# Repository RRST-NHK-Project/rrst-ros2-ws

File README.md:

# **rrst-ros2-workspace**

**日本語** | [English](README.en.md)

## 1. 概要
NHK プロジェクトのメインリポジトリです。現在使用している ROS 2 パッケージを管理しています。大会ごとにこのリポジトリをforkして使用することを想定しています。

|  | 説明 | ビルド状況 |
|---|---|---|
| **main** | 安定版ブランチ（動作確認済み） |  |
| **develop** | 最新の開発ブランチ（開発中） |  |
| **Docker** | Docker ビルド（develop） |  |

---

## 2. 動作環境

| 項目 | 内容 |
|:---|:---|
| OS | Ubuntu 24.04 LTS |
| ROS | ROS 2 Jazzy |
| メモリ | 16 GB 以上推奨 |

> **注意**: ビルド中にフリーズする場合は、メモリ不足の可能性があります。  
> スワップ領域を追加するか、ビルドのスレッド数を制限してください。

---

## 3. はじめに

### 3.1 ワークスペースの作成
作成済みの場合はスキップしてください。

    mkdir -p ~/ros2_ws/src

### 3.2 SSH 鍵の登録
リポジトリ・サブモジュールとも **SSH** で運用しています。登録済みの場合はスキップしてください。

    ssh-keygen -t ed25519 -C "your_email@example.com"
    cat ~/.ssh/id_ed25519.pub

表示された公開鍵を GitHub の [Settings → SSH and GPG keys](https://github.com/settings/keys) で **New SSH key** から登録し、接続を確認します。

    ssh -T git@github.com

`Hi <ユーザー名>! You've successfully authenticated...` と表示されれば完了です。詳しくは [Wiki](https://github.com/RRST-NHK-Project/rrst-ros2-ws/wiki/SSH鍵の登録) を参照してください。

### 3.3 リポジトリのクローン

**main（安定版）**

    cd ~/ros2_ws/src
    git clone git@github.com:RRST-NHK-Project/rrst-ros2-ws.git .
    git submodule update --init --recursive

**develop（最新・開発中）**

    cd ~/ros2_ws/src
    git clone git@github.com:RRST-NHK-Project/rrst-ros2-ws.git -b develop .
    git submodule update --init --recursive

### 3.4 ビルド

    cd ~/ros2_ws
    colcon build

ビルドのスレッド数を指定する場合:

    cd ~/ros2_ws
    colcon build --parallel-workers 4

---

## 4. クレジット
Developed by NHK Project, RRST, Ritsumeikan University, Japan (2024)
- 公式サイト: https://www.rrst.jp
- X (Twitter): https://x.com/RRST_BKC

---

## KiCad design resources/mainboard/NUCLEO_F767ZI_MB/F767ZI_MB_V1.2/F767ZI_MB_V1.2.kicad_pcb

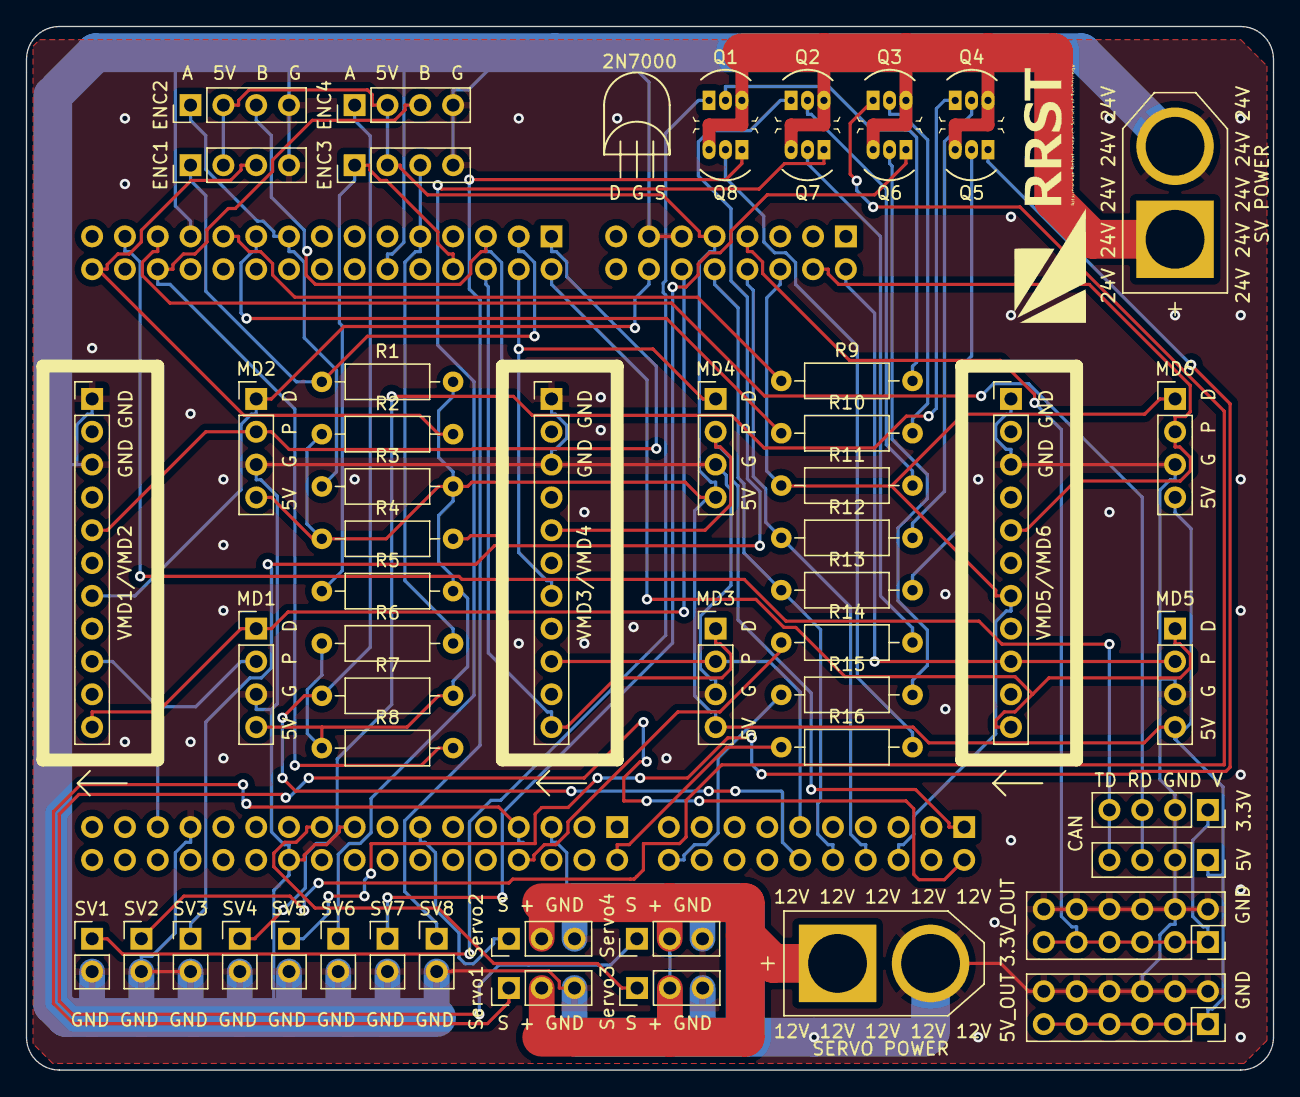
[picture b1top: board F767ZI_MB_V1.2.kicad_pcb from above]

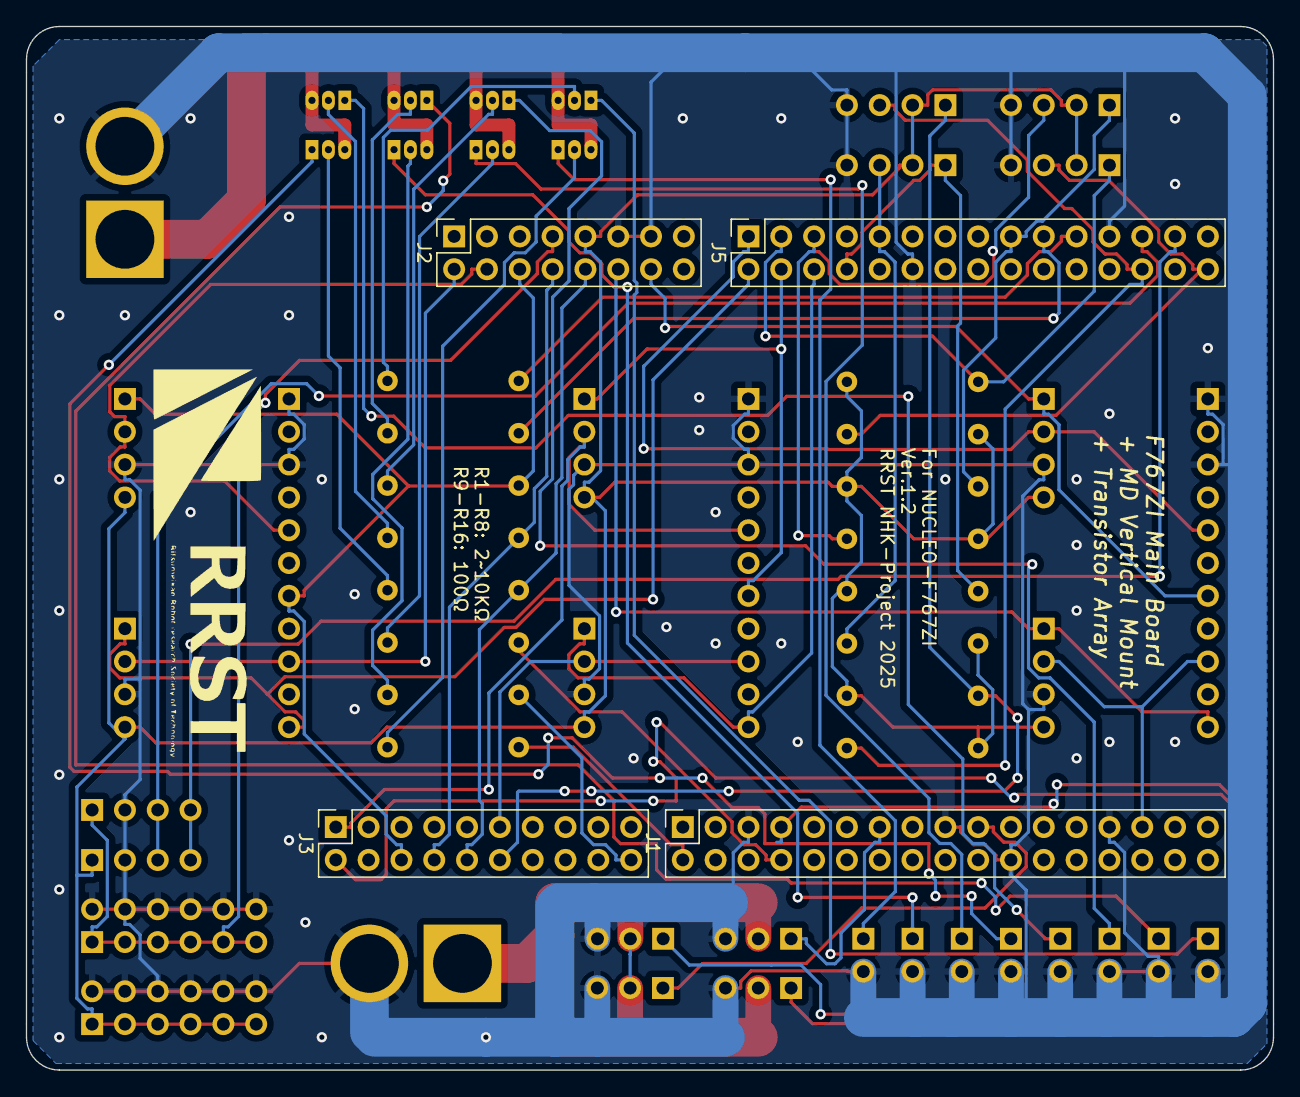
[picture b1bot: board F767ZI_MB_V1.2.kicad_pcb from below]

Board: 2 copper layers, 96.5 x 80.8 mm, 59 parts (4 on the bottom side), 54 nets.

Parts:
3.3V: CAN3.3V; PinSocket_1x04_P2.54mm_Vertical
3.3V_OUT: 3.3V_OUT; PinSocket_2x06_P2.54mm_Vertical
5V: CAN5V; PinSocket_1x04_P2.54mm_Vertical
5V_OUT: 5V_OUT; PinSocket_2x06_P2.54mm_Vertical
ENC1: ENC1; PinHeader_1x04_P2.54mm_Vertical
ENC2: ENC2; PinHeader_1x04_P2.54mm_Vertical
ENC3: ENC3; PinHeader_1x04_P2.54mm_Vertical
ENC4: ENC4; PinHeader_1x04_P2.54mm_Vertical
J1: Conn_02x17_Odd_Even; PinHeader_2x17_P2.54mm_Vertical
J2: Conn_02x08_Odd_Even; PinHeader_2x08_P2.54mm_Vertical
J3: Conn_02x10_Odd_Even; PinHeader_2x10_P2.54mm_Vertical
J5: Conn_02x15_Odd_Even; PinHeader_2x15_P2.54mm_Vertical
MD1: MD1; PinHeader_1x04_P2.54mm_Vertical
MD2: MD2; PinHeader_1x04_P2.54mm_Vertical
MD3: MD3; PinHeader_1x04_P2.54mm_Vertical
MD4: MD4; PinHeader_1x04_P2.54mm_Vertical
MD5: MD5; PinHeader_1x04_P2.54mm_Vertical
MD6: MD6; PinHeader_1x04_P2.54mm_Vertical
Q1, Q2, Q3, Q4, Q5, Q6, Q7, Q8: 2N7000; TO-92-3
R1, R2, R3, R4, R5, R6, R7, R8, R9, R10, R11, R12, R13, R14, R15, R16: R; R_Axial_DIN0207_L6.3mm_D2.5mm_P10.16mm_Horizontal
SERVO POWER: XT60-M; AMASS_XT60-M
SV1: SV1; PinHeader_1x02_P2.54mm_Vertical
SV2: SV2; PinHeader_1x02_P2.54mm_Vertical
SV3: SV3; PinHeader_1x02_P2.54mm_Vertical
SV4: SV4; PinHeader_1x02_P2.54mm_Vertical
SV5: SV5; PinHeader_1x02_P2.54mm_Vertical
SV6: SV6; PinHeader_1x02_P2.54mm_Vertical
SV7: SV7; PinHeader_1x02_P2.54mm_Vertical
SV8: SV8; PinHeader_1x02_P2.54mm_Vertical
SV POWER: XT60-M; AMASS_XT60-M
Servo1: Servo1; PinHeader_1x03_P2.54mm_Vertical
Servo2: Servo2; PinHeader_1x03_P2.54mm_Vertical
Servo3: Servo3; PinHeader_1x03_P2.54mm_Vertical
Servo4: Servo4; PinHeader_1x03_P2.54mm_Vertical
VMD1/VMD2: VMD1/VMD2; PinHeader_1x11_P2.54mm_Vertical
VMD3/VMD4: VMD3/VMD4; PinHeader_1x11_P2.54mm_Vertical
VMD5/VMD6: VMD5/VMD6; PinHeader_1x11_P2.54mm_Vertical

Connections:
+3.3V: 3.3V.1, 3.3V_OUT.1, 3.3V_OUT.3, 3.3V_OUT.5, 3.3V_OUT.7, 3.3V_OUT.9, 3.3V_OUT.11, J2.7
+5V: 5V.1, 5V_OUT.1, 5V_OUT.3, 5V_OUT.5, 5V_OUT.7, 5V_OUT.9, 5V_OUT.11, ENC1.2, ENC2.2, ENC3.2, ENC4.2, J2.9, MD1.4, MD2.4, MD3.4, MD4.4, MD5.4, MD6.4, R1.2, R2.1, R3.2, R4.1, R5.2, R6.1, R7.2, R8.1
GND: 3.3V.2, 3.3V_OUT.2, 3.3V_OUT.4, 3.3V_OUT.6, 3.3V_OUT.8, 3.3V_OUT.10, 3.3V_OUT.12, 5V.2, 5V_OUT.2, 5V_OUT.4, 5V_OUT.6, 5V_OUT.8, 5V_OUT.10, 5V_OUT.12, ENC1.4, ENC2.4, ENC3.4, ENC4.4, J1.5, J1.17, J1.22, J1.27, J2.11, J2.13, J5.12, J5.23, MD1.3, MD2.3, MD3.3, MD4.3, MD5.3, MD6.3, SERVO POWER.N (NEG), SV1.2, SV2.2, SV3.2, SV4.2, SV5.2, SV6.2, SV7.2, SV8.2, SV POWER.N (NEG), Servo1.3, Servo2.3, Servo3.3, Servo4.3, VMD1/VMD2.1, VMD1/VMD2.3, VMD3/VMD4.1, VMD3/VMD4.3, VMD5/VMD6.1, VMD5/VMD6.3
unnamed: Q1.2 (G), R9.2
unnamed: Q1.1 (S), SV1.1
unnamed: Q2.2 (G), R11.2
unnamed: Q2.1 (S), SV3.1
unnamed: Q3.2 (G), R10.2
unnamed: Q3.1 (S), SV2.1
unnamed: Q4.2 (G), R12.2
unnamed: Q4.1 (S), SV4.1
unnamed: Q5.2 (G), R13.2
unnamed: Q5.1 (S), SV5.1
unnamed: Q6.2 (G), R15.2
unnamed: Q6.1 (S), SV7.1
unnamed: Q7.2 (G), R14.2
unnamed: Q7.1 (S), SV6.1
unnamed: Q8.2 (G), R16.2
unnamed: Q8.1 (S), SV8.1
PA_0: J1.29, MD1.2, VMD1/VMD2.9
PA_3: J5.1, MD2.2, VMD1/VMD2.5
PA_6: ENC4.1, J3.12, R7.1
PB_1: J1.7, Servo1.1
PB_6: J1.13, Servo2.1
PB_8: J3.2, Servo4.1
PC_0: ENC1.1, J5.3, R1.1
PC_3: ENC2.3, J5.5, R4.2
PC_6: J3.1, MD4.2, VMD3/VMD4.5
PC_7: J3.11, MD3.2, VMD3/VMD4.9
PC_8: J2.2, MD5.2, VMD5/VMD6.9
PC_9: J2.4, MD6.2, VMD5/VMD6.5
PC_10: J2.6, J3.6, MD6.1, R11.1, VMD5/VMD6.7
PC_11: J2.8, J3.8, R12.1
PC_12: J2.10, J3.10, R13.1
PD_0: 3.3V.3, 5V.3, J5.25
PD_1: 3.3V.4, 5V.4, J5.27
PD_2: J2.12, MD1.1, VMD1/VMD2.11
PD_4: ENC3.1, J5.8, R5.1
PD_5: J5.6, MD3.1, VMD3/VMD4.11
PD_6: J5.4, MD4.1, VMD3/VMD4.7
PD_7: J5.2, MD5.1, VMD5/VMD6.11
PD_13: J1.19, Servo3.1
PF_0: J5.21, R9.1
PF_1: J5.19, R10.1
PF_2: ENC2.1, J5.17, R3.1
PF_5: ENC3.3, J5.9, R6.2
PF_7: ENC4.3, J5.26, R8.2
PF_12: J3.20, R15.1
PF_13: J1.2, R16.1
PF_14: J1.8, R14.1
PG_1: ENC1.3, J5.30, R2.2
PG_2: J2.14, MD2.1, VMD1/VMD2.7
SERVO+: SERVO POWER.P (POS), Servo1.2, Servo2.2, Servo3.2, Servo4.2
TR+: Q1.3 (D), Q2.3 (D), Q3.3 (D), Q4.3 (D), Q5.3 (D), Q6.3 (D), Q7.3 (D), Q8.3 (D), SV POWER.P (POS)

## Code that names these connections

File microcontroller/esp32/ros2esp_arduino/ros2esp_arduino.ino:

#include <ESP32Encoder.h>

/*
2025, RRST-NHK-Project
ros2espパッケージ、マイコン側プログラム
microROSで受信したデータをもとにピン操作
ワイヤレスデバッグ(Bluetooth Serial)に対応しています。ROS側からオンオフ切り替えできます。スマホアプリもしくはTeratermでデバッグ可能です。
４MB版のESPでは容量が不足するためTools/PartitionSchemeからNO OTA(2MB APP/2MB SPIFFS)を選択してください。

TODO:時間経過でスタックするバグの修正

*/

//microROS関連
#include <micro_ros_arduino.h>
#include <rcl/rcl.h>
#include <rcl/error_handling.h>
#include <rclc/rclc.h>
#include <rclc/executor.h>
#include <std_msgs/msg/int32_multi_array.h>

//ワイヤレスデバッグで使う
#include "BluetoothSerial.h"
BluetoothSerial SerialBT;

#define MAX_ARRAY_SIZE 19

// ピンの定義 //

//通信状態表示
#define LED 2

// #define MD1P PA_0
// #define MD2P PA_3
// #define MD3P PC_7
// #define MD4P PC_6
// #define MD5P PC_8
// #define MD6P PC_9

// // MD DIR
// #define MD1D PD_2
// #define MD2D PG_2
// #define MD3D PD_5
// #define MD4D PD_6
// #define MD5D PD_7
// #define MD6D PC_10

// // サーボ
// #define SERVO1 PB_1
// #define SERVO2 PB_6
// #define SERVO3 PD_13
// #define SERVO4 PB_8

// // トランジスタ（ソレノイド・表示灯）
// #define TR1 PF_0
// #define TR2 PF_1
// #define TR3 PF_15
// #define TR4 PC_11
// #define TR5 PC_12
// #define TR6 PF_14
// #define TR7 PF_12
// #define TR8 PF_13

rcl_subscription_t subscriber;
std_msgs__msg__Int32MultiArray msg;
rclc_executor_t executor;
rclc_support_t support;
rcl_allocator_t allocator;
rcl_node_t node;
int32_t buffer[MAX_ARRAY_SIZE];

// ★ 受信データ格納用（グローバル）
volatile int32_t received_data[MAX_ARRAY_SIZE];  // 最新の受信データ
volatile size_t received_size = 0;               // 受信データのサイズ

#define RCCHECK(fn) \
  { \
    if ((fn) != RCL_RET_OK) error_loop(); \
  }

void error_loop() {
  while (1) {
    SerialBT.println("RCL Error!");
    delay(1000);
  }
}

// ★ コールバック内でグローバル変数にコピー
void subscription_callback(const void *msgin) {
  const std_msgs__msg__Int32MultiArray *msg = (const std_msgs__msg__Int32MultiArray *)msgin;

  size_t len = msg->data.size;
  if (len > MAX_ARRAY_SIZE) len = MAX_ARRAY_SIZE;

  for (size_t i = 0; i < len; i++) {
    received_data[i] = msg->data.data[i];
  }

  received_size = len;
}

void setup() {
  SerialBT.begin("ESP32");
  delay(2000);

  set_microros_transports();

  allocator = rcl_get_default_allocator();

  //通信状態表示LED
  pinMode(LED, OUTPUT);
  digitalWrite(LED, HIGH);

  // ★ エージェントと接続できるまでリトライ
  while (rclc_support_init(&support, 0, NULL, &allocator) != RCL_RET_OK) {
    SerialBT.println("Waiting for agent...");
    delay(1000);  // 1秒待つ
  }

  RCCHECK(rclc_node_init_default(&node, "micro_ros_esp_node_00", "", &support));
  RCCHECK(rclc_subscription_init_default(
    &subscriber,
    &node,
    ROSIDL_GET_MSG_TYPE_SUPPORT(std_msgs, msg, Int32MultiArray),
    "mr_swerve_drive"));

  std_msgs__msg__Int32MultiArray__init(&msg);
  msg.data.data = buffer;
  msg.data.size = 0;
  msg.data.capacity = MAX_ARRAY_SIZE;

  RCCHECK(rclc_executor_init(&executor, &support.context, 1, &allocator));
  RCCHECK(rclc_executor_add_subscription(&executor, &subscriber, &msg, &subscription_callback, ON_NEW_DATA));

  // ピンの初期化 //

  // MD DIR
  // pinMode(MD1P, OUTPUT);
  // pinMode(MD2P, OUTPUT);
  // pinMode(MD3P, OUTPUT);
  // pinMode(MD4P, OUTPUT);
  // pinMode(MD5P, OUTPUT);
  // pinMode(MD6P, OUTPUT);

  // // MD PWM
  // pinMode(MD1D, OUTPUT);
  // pinMode(MD2D, OUTPUT);
  // pinMode(MD3D, OUTPUT);
  // pinMode(MD4D, OUTPUT);
  // pinMode(MD5D, OUTPUT);
  // pinMode(MD6D, OUTPUT);

  // // サーボ
  // pinMode(SERVO1, OUTPUT);
  // pinMode(SERVO2, OUTPUT);
  // pinMode(SERVO3, OUTPUT);
  // pinMode(SERVO4, OUTPUT);

  // // トランジスタ(ソレノイド・表示灯)
  // pinMode(TR1, OUTPUT);
  // pinMode(TR2, OUTPUT);
  // pinMode(TR3, OUTPUT);
  // pinMode(TR4, OUTPUT);
  // pinMode(TR5, OUTPUT);
  // pinMode(TR6, OUTPUT);
}

void loop() {
  RCCHECK(rclc_executor_spin_some(&executor, RCL_MS_TO_NS(5)));

  digitalWrite(LED, HIGH);

  //以下メインの処理

  //デバッグ用
  if (received_data[0] == 1) {
    SerialBT.print("Received: ");
    for (size_t i = 0; i < received_size; i++) {
      SerialBT.print(received_data[i]);
      SerialBT.print(", ");
    }
    SerialBT.println();
  }

  //ピンの操作

  //ここまで

  //delay(10);
}

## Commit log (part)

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2026-04-10 PIDで壁と平行になりました。
2026-04-10 Update subproject commit reference in rrst-console
2026-04-10 壁上りを角度が平行じゃない状態からする。
2026-04-11 真偽のtopic飛ばせるようになりました
2026-04-11 とりあえず通信周りと雛形だけ実装
2026-04-11 コメント＆データ＆タスク整理
2026-04-12 動作まわり実装
2026-04-13 mediapipeによるジェスチャー検知の移植
2026-04-13 状態名の実装
2026-04-13 状態遷移実装
2026-04-13 経路計画からの旋回動作を統合
2026-04-14 AutoDriveのリセット
2026-04-14 MFFモードと平面モードでのノード選択
2026-04-14 旋回指令の統合、状態切り替えの半自動化が必要
2026-04-14 一連の流れv1（設定のエクスポート）
2026-04-14 同梱serial_bridgeの更新
2026-04-14 ノード名を変更
2026-04-14 Update serial_bridge subproject to latest commit
2026-04-15 R2モノレール完成。あと配線のみ。。。配線配線配線配線配線配線配線。。。。。
2026-04-15 細かい変更
2026-04-15 serial_bridge簡易GUIの作成
2026-04-15 レイアウト崩れを修正
2026-04-15 通信量のモニタを追加
2026-04-15 視認性の向上
2026-04-15 Fオドメトリのエンコーダパルス反転
2026-04-15 スタッフハンドちょい触り
2026-04-15 段差超え現状
2026-04-16 動かない...
2026-04-16 KFS姿勢推定
2026-04-16 タブ名称の変更
2026-04-16 整理かつ調整
2026-04-16 マスク指定のトピック入力を追加
2026-04-16 KFS位置合わせ用の状態追加
2026-04-16 R2ハンド微調整
2026-04-16 一旦提出
2026-04-16 コメント削除
2026-04-17 マイコンのデータ問題解決次第R1タスク終了
2026-04-17 段差超え克服
2026-04-17 色々追加。動作確認なし。
2026-04-18 一旦撤退。
2026-04-19 カメラのサーボ動くようになりました。まだ要調整必要。cubeと平行になるのはうまくいけてない。
2026-04-19 Update subproject commit reference in serial_bridge
2026-04-20 立方体検知とAKAZEの統合v1
2026-04-20 パラメータの受取まわりの修正
2026-04-20 realsenseの警告に対処
2026-04-20 一旦テスト
2026-04-20 大量追加
2026-04-20 参照ミスの修正
2026-04-20 ローカルで試したいよね
2026-04-20 パラメータ調整２
2026-04-20 中心バイアスの除去
2026-04-20 令和最新版
2026-04-20 立方体検知にフィルタ追加
2026-04-20 令和最新版は信赖 てき る
2026-04-20 これでどうでしょう
2026-04-20 びるどとおした
2026-04-20 一旦KFS位置合わせ。YAW軸が弱い
2026-04-20 YAW軸をちょいと追加
2026-04-20 YAW軸合わせを最後に
2026-04-20 令和改良版
2026-04-20 コメント追加
2026-04-20 launch一括起動スクリプトの作成
2026-04-20 R1マガジン角度調整
2026-04-20 オフセット追加ぶつかるときあり
2026-04-21 即時遷移（200ms）
2026-04-21 R2機構制御をr2_mcに統合
2026-04-21 デバッグ出力の調整
2026-04-21 R2自己診断パッケージ（とりあえず形のみ）
2026-04-21 realsense版ArUcoトラッカー（未検証）
2026-04-21 不要パラメータの削除
2026-04-21 joy外し
2026-04-21 手動要素の排除
2026-04-21 一旦一個
2026-04-21 r2_hw_ctrlパッケージのlaunch整備
2026-04-21 KFSシーケンス変更。
2026-04-22 プランナーのパラメータを抽出
2026-04-22 launch定義
2026-04-22 tmuxの導入
2026-04-22 tmux版起動スクリプト（若干つかいにくい）
2026-04-22 自己診断パッケージの中身を少し
2026-04-22 realsenseでKFS検知V１
2026-04-22 HSVマスク＋輪郭抽出＋ホモグラフィー変換＋AKAZE特徴抽出 辞書精度は悪いがKFS検出は高精度
2026-04-22 ID3用node追加
2026-04-22 起動順により状態名解決できないバグを修正
2026-04-22 wasu
2026-04-22 QoS調整が終わらない
2026-04-22 キャッシュ削除
2026-04-22 苦しんで覚えるQoS
2026-04-22 原因のcallback関数を修正
2026-04-22 AIに勝利
2026-04-22 帰りたい。。。
2026-04-22 足の準備できました
2026-04-22 ヘッドハンドの状態管理
2026-04-22 tyousei
2026-04-22 段差超えシーケンスの完了フラッグを追加
2026-04-22 フラッグからのマス進行
2026-04-22 アリーナモード追加
2026-04-22 え？まさか、、、？
2026-04-22 Switch2対応
2026-04-22 LD19から８方位の距離を抽出するパッケージ
2026-04-22 mistake
2026-04-22 プロンプト代行
2026-04-22 400mm保持を削除
2026-04-22 フロント値を使用するように変更
2026-04-22 角度PIDに切り替え
2026-04-22 アリーナシーケンスを修正
2026-04-22 符号変更
2026-04-22 現状その二
2026-04-22 switch1と2入れ替え
2026-04-22 リミット数変更
2026-04-22 旋回が反転できない
2026-04-22 旋回方向の修正？
2026-04-23 arena_auto_hybrid
2026-04-23 アリーナノードトリガー変更
2026-04-23 ひとまずアリーナ第一段階突破
2026-04-23 途中状態からの状態自動遷移
2026-04-23 アリーナモードでのロックとロック解除フラッグの設定
2026-04-23 疑似コマンドの修正
2026-04-23 アリーナモードの自動モトリガー
2026-04-23 状態遷移ロックの干渉問題
2026-04-23 経路不足でのフォールバックを外す
2026-04-23 モードの強制代入を削除
2026-04-23 更新サブプロジェクトのコミットID
2026-04-23 ダメ元修正
2026-04-23 これでモノレール治ったはず...
2026-04-23 mff_step_cmdの常時publish
2026-04-23 段差下り2回めが不具合発生
2026-04-23 問題解決？
2026-04-23 Fix formatting of arena_left_mm_ variable declaration
2026-04-23 R2一連の流れ、アリーナ含む
2026-04-24 超進捗：KFS回収成功
2026-04-24 上ボタンを押すごとにKFSシーケンス動く。下ボタンで一つ前に戻る。シーケンス終了後に上ボタンを押すとまたはじめに戻る。
2026-04-24 KFS改良版
2026-04-24 ２次ビここまで！
2026-04-27 KFSシーケンス高さごとに再度分けた
2026-04-28 Update rrst-console subproject to latest commit 2c548b9
2026-04-29 Refactor TaskManagerNode: Remove MFF-related functionality and introduce magazine action handling
    - Removed MFF cell management and related structures from task_manager_node.hpp and task_manager_node.cpp.
    - Updated launch file to remove MFF-related parameters and added magazine action topic.
    - Introduced handling for magazine actions in TaskManagerNode, including validation and logging.
    - Cleaned up subscriptions and publishers to reflect the removal of MFF functionality.
    - Adjusted status publishing to exclude MFF cell information.
2026-04-29 UI修正
2026-04-29 Update subproject commits for rrst-console and serial_bridge
2026-04-29 Update serial_bridge subproject to latest commit 7d8ccb6
2026-04-29 手動モード時の足回りの管理ノードをr2_autoへ変更
2026-04-29 ログの整理
2026-04-29 状態管理の整理、大規模改修前バックアップ
2026-04-29 状態経路の統合と再整備（大規模改修）
2026-04-29 足回りの管理権限が移譲されないバグの修正１
2026-04-29 QoS不一致の解決
2026-04-29 モードの混線を除去
2026-04-29 r2_autoがモードを受け付けないバグを修正
2026-04-29 ログ追加
2026-04-29 【状態経路の再整備】
2026-04-29 モードの混線を解決したい
2026-04-29 混乱の元を消していこう
2026-04-29 一旦安定？明日デバッグ作業します
2026-04-29 コントローラとの共存
2026-05-01 CANtest
2026-05-01 R2_AutoのL1、R1を削除
2026-05-01 Update subproject commit references in rrst-console and serial_bridge
2026-05-01 r2_mcのモード上書きの除去
2026-05-01 PSボタンで自動遷移が有効になる不具合を修正
2026-05-01 R1問題解消！
2026-05-01 R1マガジン初期化コマンド実装＿現在コメントアウト中＿AIに頼らず頑張ります
2026-05-02 R1マガジンポール固定機構の角度調整
2026-05-02 角度など調整
2026-05-02 段差超え、降りのUP、DOWNをTRIANGLE、CROSSに変更
2026-05-07 Update subproject commit reference in microcontroller-ws
2026-05-07 READMEの更新
    Added detailed project overview, system requirements, and getting started instructions.
2026-05-07 Add MIT License to the project
2026-05-07 ファイル整理とライセンス変更
2026-05-12 速度PID（低速域）
2026-05-13 cr26かいし
2026-05-14 ボタンで回るだけ
2026-05-19 コントローラ周り追加
2026-05-19 ほぼ動くinput関連まだ
2026-05-20 add sw
2026-05-20 half
2026-05-20 update submodule references for rrst-console and serial_bridge
2026-05-21 微分先行型P-D制御ライブラリと共通ライブラリの整備
2026-05-21 serial_bridge_v2
2026-05-21 Remove untracked or incorrectly mapped serial_bridge_v2 directory
2026-05-21 update submodule reference for serial_bridge
2026-05-21 update submodule references for microcontroller-ws and serial_bridge
2026-05-21 pptxに対応
2026-05-28 update submodule reference for microcontroller-ws
2026-05-28 魔改造ESC第一弾
2026-05-28 発散したし収束する値もおかしい
2026-05-28 少し収束ミス
2026-06-01 なんか良さげ？
2026-06-03 コンソールからのゲイン調整
2026-06-09 定期メンテ
2026-06-09 force push
2026-06-09 Update subproject commits for microcontroller-ws and serial_bridge
2026-06-10 速度指令をRPMに統一
2026-06-10 ESC関連の仲介ノードを整備１
2026-06-10 pcnt count -> degree
2026-06-10 Update subproject commit for serial_bridge
2026-06-26 esc param?
